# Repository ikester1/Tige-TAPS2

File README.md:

# Replacement Tige TAPS Trim Controller

This is a replacement for the original trim controller for an early 2000's [Tige](https://www.tige.com/) 22v wakeboard boat.
The *electric actuator* is made by [Lenco](https://www.lencomarine.com), the Tige logo'd
trim indicator gauge is probably made by [Faria](https://fariabeede.com), and the
"black box" controller is under the dashboard.  The "black box" takes the trim switch input and drives the actuator
and gauge.  Coupled with a plate on the transom, Tige called the entire system **TAPS2**.

The original controller is prone to failure, and is no longer available from Lenco or Tige.  There are
other solutions from Lenco but there are none which retain the use of the original trim switch and Tige
gauge.

Tige's TAPS controller fully retracts the actuator at each start so one must
reposition the trim at every restart.
This project improves on the original implementation by saving the final actuator position for the next
restart.
If everything works right, the trim will not move and the gauge will be correctly positioned when the
boat is restarted.

The controller's external connections are power and ground, trim switch top/middle/bottom,
gauge power/ground/signal, and two actuator motor power leads.  The controller box has a lighted
setup pushbutton and redundant trim switch.
The box, while deeper than the original controller, has the same footprint.

This project includes the controller's schematic diagram and PCB layout, a 3D printable enclosure, and the C++
controller software.  With access to a 3D printer, the cost of the controller should be less than $75.

# Making the Controller

The replacement controller is a custom processor board connected to a commercial
[H-Bridge](https://en.wikipedia.org/wiki/H-bridge)
to switch the relatively high current actuator connections.
The processor board holds a [Raspberry Pi Pico](https://www.google.com/search?q=raspberry+pico) and surrounding
glue circuitry.

## Processor Board

The [pcb](pcb) directory holds the [KiCad 6](https://www.kicad.org/) files detailing the schematic and
printed circuit layout, and
[bin/TAPS.zip](bin)
is a
[Gerber](https://en.wikipedia.org/wiki/Gerber_format)
file to send to a printed circuit board
fabricator such as [OSHPARK](https://oshpark.com/).

Almost all components are available at [Digi-Key](https://www.digikey.com/) and the schematic is annotated with
manufacturer and product numbers for each component.
The Pico power supply is from [adafruit](https://www.adafruit.com/product/4683).
In addition to the usual soldering supplies, a special crimper
( [Amazon](https://www.amazon.com/dp/B088NQV8Z3) )
is needed for the board's connectors though
one could skip the connectors and solder the wires to the boards.

## H-Bridge

The commercial H-Bridge is a BTS7960 43A High Power Motor Driver Module and can be purchased on Amazon for less than $10 from
[several souces](https://www.amazon.com/s/?url=search-alias%3Daps&field-keywords=BTS7960+43A+Motor+Driver+Module).
The H-Bridge board has an 8 pin header for its logic connections to the processor board; replace this header with the same locking connector
as the processor board to improve robustness.

## Code

The C++ code is compiled on Linux with the [Raspberry Pi Pico C/C++ SDK](https://datasheets.raspberrypi.com/pico/raspberry-pi-pico-c-sdk.pdf).
Go to the [src](src) directory, type `cmake -B build` followed by `cd build && make` to generate the executable to
copy to the Pico processor as described in the SDK. The most recent executable is [bin/taps.elf](bin).

## Enclosure and Switches

The [box](box) directory holds the [SketchUp](https://www.sketchup.com/) enclosure design files.
[Cura](https://ultimaker.com/software/ultimaker-cura) successfully slices
[bin/boxBottom.stl](bin) and [bin/boxTop.stl](bin)
for an [Ultimaker 3D printer](https://ultimaker.com/) though other slicers and printers should work.
The ABS enclosure's bottom secures the boards and external wires with 2-56 screws, while the top holds the setup button and
auxiliary trim switch.
The auxiliary trim switch is a duplicate of the button used on the throttle of the Tige boat.
It is manufactured by
[E-Switch](https://www.e-switch.com/),
part number
R1966IBLKREDEF,
and available on
[Digi-Key](https://www.digikey.com/short/t0br9zjr)
as part number [EG5445-ND](https://www.digikey.com/short/t0br9zjr).
The 16mm illumated setup pushbutton is available from [adafruit](https://www.adafruit.com/product/1477)
and [amazon](https://www.amazon.com/dp/B0148183D2).

The box top and bottom are held together with two 6.3mm automotive plastic trim fasteners.

## Connections

Connect the three *gauge* wires to the existing Tige TAPS gauge -- these should be the only wires connected to
the gauge terminal posts.  This new black box supplies power to the gauge; **do not** also connect the gauge's power terminal to
the boat's electrical system.  Looking from the rear, the black box gauge *PWR* leads goes on the right, *GND* goes in the middle,
and *SIG* goes on the left.  **Connecting any power lead to the gauge's *SIG* terminal will damage the gauge.**
The spade terminal near the blue cap is for gauge illumination and this connection should go to the lighting circuit
shared with the other instruments.

Connect the black box's two actuator leads to the two leads coming from the Lenco electric actuator.  Polarity
is only important when it comes time to ensure the actuator retracts when the black box thinks it should be
retracting, and extends when the black box thinks it is extending the actuator.  If you get the leads backwards,
they can simply be plugged in the other way.

Connect the three trim switch wires to the boat's trim switch ... on my boat this switch is on the throttle handle.
There is no appreciable current flowing through the trim switch so any secure means of connection (any kind of connector)
should be fine.  Do not otherwise connect the boat's power or ground to these connections.

Finally, connect the black box's power and ground to the electrical system.  The heavy power lead should be connected, most likely,
to the same 15A breaker that was powering the original black box (actually, a 10A breaker is probably adequate).
The other, lighter, power lead should be connected to a switched power source.

# Setup

The black box has a *setup mode* entered by pressing its pushbutton.  The button's LED pulses
when the box is in *setup mode* and goes dark when *setup mode* is exited.  *Setup mode* is automatically exited after one
minute of inactivity, or if the pushbutton is pressed and held for at least two seconds.

As soon as *setup mode* is entered, the actuator should fully retract.
If the actuator extends instead of retracts, simply reverse the actuator leads and try again.
When not in
*setup mode*, pressing the side
of the rocker switch nearest the pushbutton should extend the actuator, the other side of
the rocker switch should retract it.
Similarly, pressing the top of the rocker switch on the throttle should extend the actuator and the bottom half of the
switch should retract it.  Something is wrong with the
throttle's switch or wiring if the box's rocker switch works but the throttle's does not.

The primary purpose of *setup mode* is to calibrate the TAPS gauge.
This is done by manually setting the gauge's fully retracted (wakeboard) and 25% - 50% - 75% - 100% 
extended (slalom) gauge needle positions.
More specifically, the gauge's 8, 6, 4, 2, and 0 readings are adjusted.
Enter *setup mode* to adjust these positions and use the trim switch to set the needle's **8** position.
Press the setup button and set the needle's **6** position.
Press the button and set the **4** position; continue for the **2** and **0** positions.
One should be careful when setting the **0** position: release the trim switch as soon as the
**0** position is reached (do not linger) as doing otherwise will bias the box's idea of when **0** was reached.
*Setup mode* automatically exits once the setup button is pressed after adjusting for the **0** position.

# Operation

The trim switch and TAPS system should operate exactly as the original system, except:
- The new black box remembers the actuator and gauge positions when the boat is shut down.
The original box retracts the actuator and resets the gauge at every boat restart.

- The original black box runs the actuator as long as the trim switch is pressed; this replacement box stops the actuator
once it is 50% beyond the retract or extend limits.
In any case, running the Lenco actuator beyond its limits causes no harm to the actuator.

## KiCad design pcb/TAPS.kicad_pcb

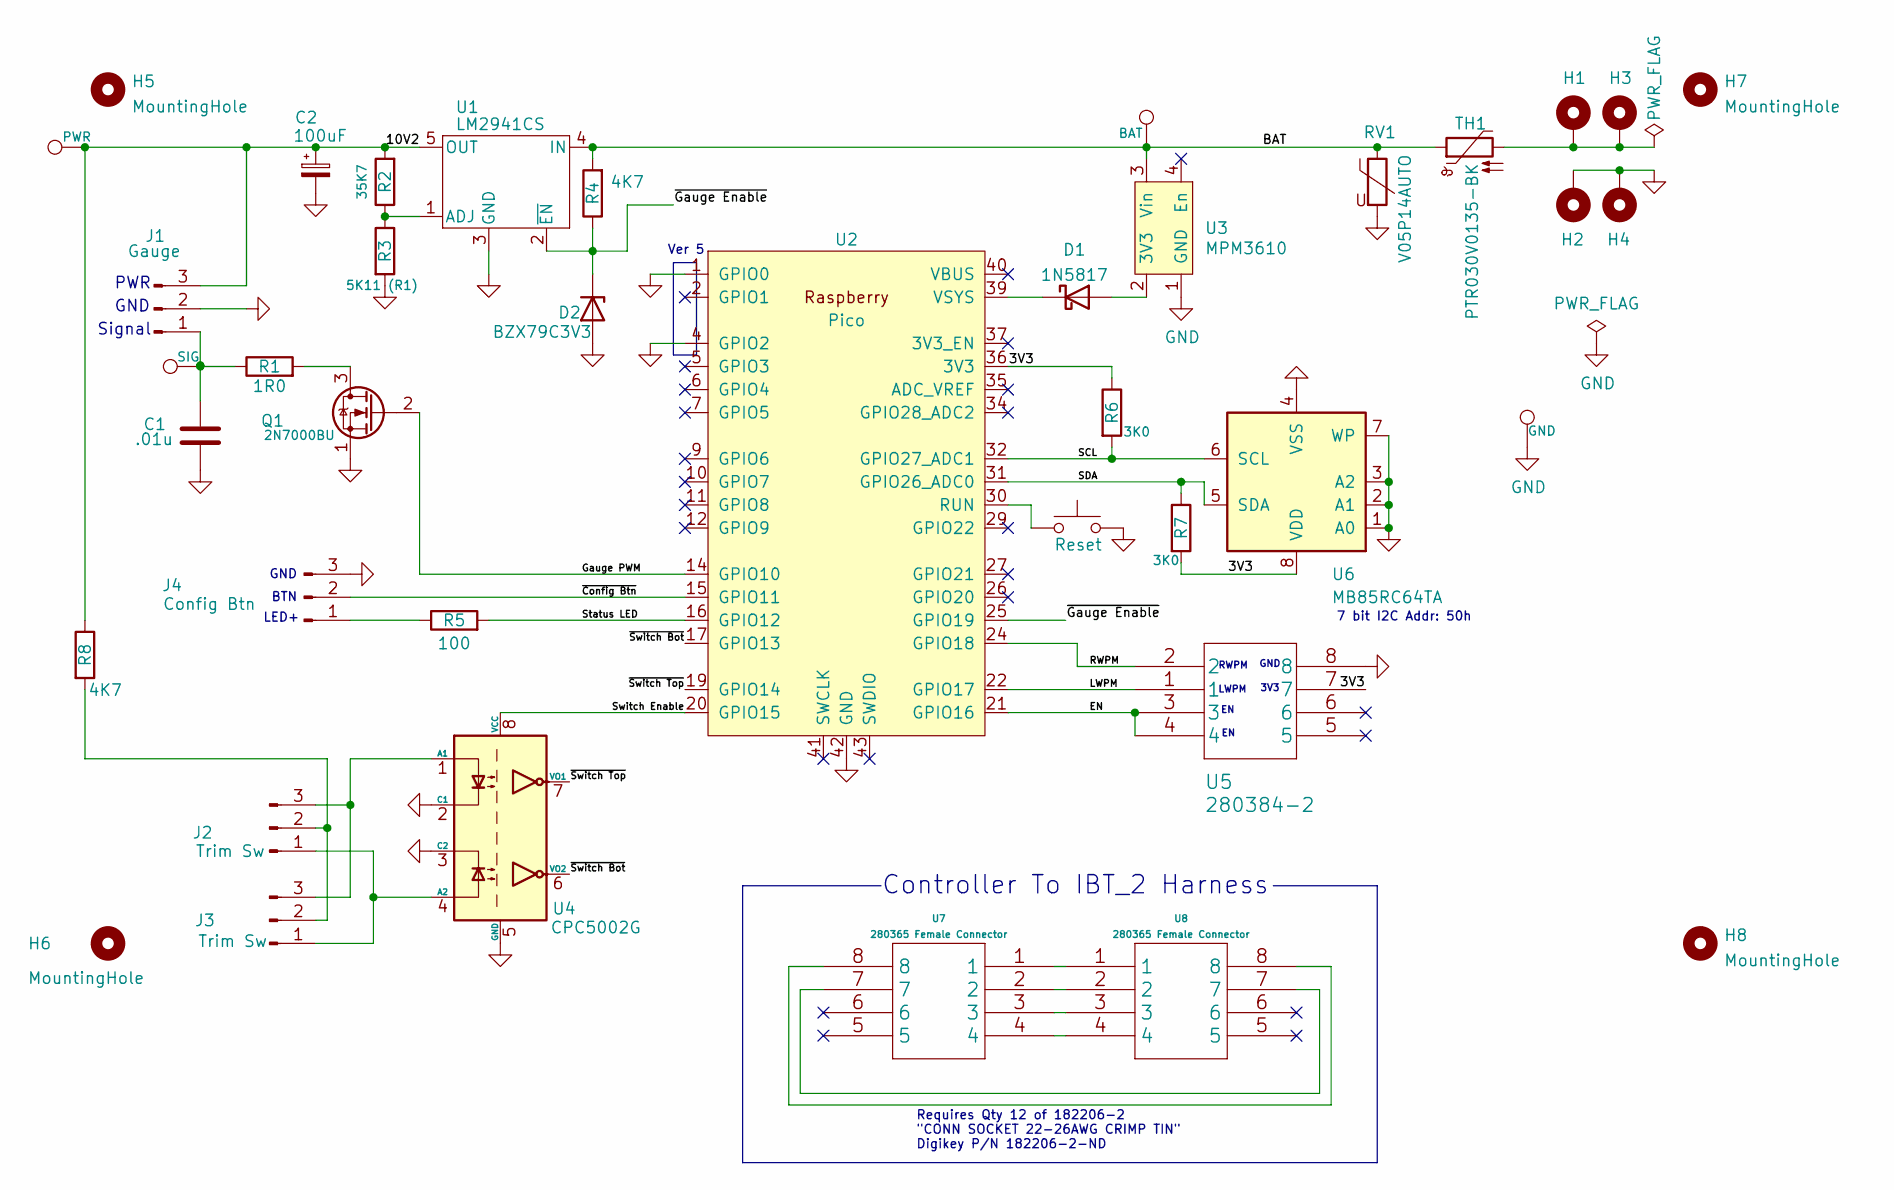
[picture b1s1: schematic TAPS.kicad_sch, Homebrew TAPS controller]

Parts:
C1: .01u; C_Disc_D4.3mm_W1.9mm_P5.00mm; Digikey PN 399-4206-ND
C2: 100uF; C_Disc_D9.0mm_W5.0mm_P5.00mm; Digikey PN 478-1847-ND
D1: 1N5817; D_A-405_P7.62mm_Horizontal; Digikey PN 1N5817RLGOSCT-ND
D2: BZX79C3V3; D_DO-34_SOD68_P7.62mm_Horizontal; Digikey PN BZX79C3V3-ND
H1, H2, H3, H4: MountingHole_Pad; MountingHole_2.5mm_Pad_TopBottom
H5, H6, H7, H8: MountingHole; MountingHole_2.5mm
J1: Gauge; JST_XH_B3B-XH-A_1x03_P2.50mm_Vertical; Digikey PN 455-1990-ND
J2, J3: Trim Sw; JST_XH_B3B-XH-A_1x03_P2.50mm_Vertical; Digikey PN 455-1990-ND
J4: Config Btn; JST_XH_B3B-XH-A_1x03_P2.50mm_Vertical
Q1: 2N7000BU; TO-92_Inline; Digikey PN 2N7000BU-ND
R1: 1R0; R_Axial_DIN0204_L3.6mm_D1.6mm_P7.62mm_Horizontal; Digikey PN CF18JT1R00CT-ND
R2: 35K7; R_Axial_DIN0204_L3.6mm_D1.6mm_P7.62mm_Horizontal; Digikey PN RNF18FTD35K7CT-ND
R3: 5K11 (R1); R_Axial_DIN0204_L3.6mm_D1.6mm_P7.62mm_Horizontal; Digikey PN 738-RNF18FTD5K11CT-ND
R4, R8: 4K7; R_Axial_DIN0204_L3.6mm_D1.6mm_P7.62mm_Horizontal; Digikey PN CF18JT4K70CT-ND
R5: 100; R_Axial_DIN0204_L3.6mm_D1.6mm_P7.62mm_Horizontal; Digikey PN CF18JT100RCT-ND
R6, R7: 3K0; R_Axial_DIN0204_L3.6mm_D1.6mm_P7.62mm_Horizontal; Digikey PN CF18JT3K00CT-ND
RV1: V05P14AUTO; C_Disc_D7.5mm_W5.0mm_P5.00mm; Digikey PN F6411-ND
SW1: Reset; SW_PUSH_6mm_H7.3mm; Digikey PN 450-1650-ND
TH1: PTR030V0135-BK; C_Disc_D10.0mm_W2.5mm_P5.00mm; Digikey PN PTR030V0135-BK-ND
TP1: PWR; TestPoint_Keystone_5000-5004_Miniature; Digikey PN 36-5002-ND
TP2: BAT; TestPoint_Keystone_5000-5004_Miniature; Digikey PN 36-5002-ND
TP3: GND; TestPoint_Keystone_5000-5004_Miniature; Digikey PN 36-5002-ND
TP4: SIG; TestPoint_Keystone_5000-5004_Miniature; Digikey PN 36-5002-ND
U1: LM2941CS; TO-263-5_TabPin3; Digikey PN LM2941CS-ND
U2: Pico; RPi_Pico_SMD; Digikey PN 2648-SC0915CT-ND
U3: MPM3610; Converter_DCDC_Adafruit_MPM3610
U4: CPC5002G; DIP-8_W7.62mm; Digikey PN CLA383-ND
U5: 280384-2; Connector_TE_280384-2; Digikey PN A106409-ND
U6: MB85RC64TA; SOP-8_3.9x4.9mm_P1.27mm; Digikey PN 865-1274-1-ND
U7, U8: 280365 Female Connector; Digikey PN A121748-ND

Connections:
/3V3: R6.1, R7.2, U2.36 (3V3), U5.7, U6.8 (VDD)
/10V2: C2.1, J1.3, R2.2, R8.1, TP1.1, U1.5 (OUT)
/BAT: R4.2, RV1.1, TH1.1, TP2.1, U1.4 (IN), U3.3 (Vin)
/EN: U2.21 (GPIO16), U5.3, U5.4
/Gauge PWM: Q1.2 (G), U2.14 (GPIO10)
/LWPM: U2.22 (GPIO17), U5.1
/RWPM: U2.24 (GPIO18), U5.2
/SCL: R6.2, U2.32 (GPIO27_ADC1), U6.6 (SCL)
/SDA: R7.1, U2.31 (GPIO26_ADC0), U6.5 (SDA)
/Status LED: R5.2, U2.16 (GPIO12)
/Switch Enable: U2.20 (GPIO15), U4.8 (VCC)
/~Config Btn: J4.2, U2.15 (GPIO11)
/~Gauge Enable: D2.1 (K), R4.1, U1.2 (~EN), U2.25 (GPIO19)
/~Switch Bot: U2.17 (GPIO13), U4.6 (VO2)
/~Switch Top: U2.19 (GPIO14), U4.7 (VO1)
GND: C1.2, C2.2, D2.2 (A), H2.1, H4.1, J1.2, J4.3, Q1.1 (S), R3.2, RV1.2, SW1.2, TP3.1, U1.3 (GND), U2.1 (GPIO0), U2.3 (GND), U2.4 (GPIO2), U2.8 (GND), U2.13 (GND), U2.18 (GND), U2.23 (GND), U2.28 (GND), U2.33 (GND), U2.38 (GND), U2.42 (GND), U3.1 (GND), U4.2 (C1), U4.3 (C2), U4.5 (GND), U5.8, U6.1 (A0), U6.2 (A1), U6.3 (A2), U6.4 (VSS), U6.7 (WP)
unnamed: C1.1, J1.1, R1.1, TP4.1
unnamed: D1.1 (K), U2.39 (VSYS)
unnamed: D1.2 (A), U3.2 (3V3)
unnamed: H1.1, H3.1, TH1.2
unnamed: J2.1, J3.1, U4.4 (A2)
unnamed: J2.2, J3.2, R8.2
unnamed: J2.3, J3.3, U4.1 (A1)
unnamed: J4.1, R5.1
unnamed: Q1.3 (D), R1.2
unnamed: R2.1, R3.1, U1.1 (ADJ)
unnamed: SW1.1, U2.30 (RUN)
unnamed: U7.1, U8.1
unnamed: U7.2, U8.2
unnamed: U7.3, U8.3
unnamed: U7.4, U8.4
unnamed: U7.7, U8.7
unnamed: U7.8, U8.8

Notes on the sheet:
Signal
3V3
7 bit I2C Addr: 50h
RWPM
BTN
Requires Qty 12 of 182206-2 "CONN SOCKET 22-26AWG CRIMP TIN" Digikey P/N 182206-2-ND
GND
Ver 5
LED+
LWPM
Controller To IBT_2 Harness
PWR

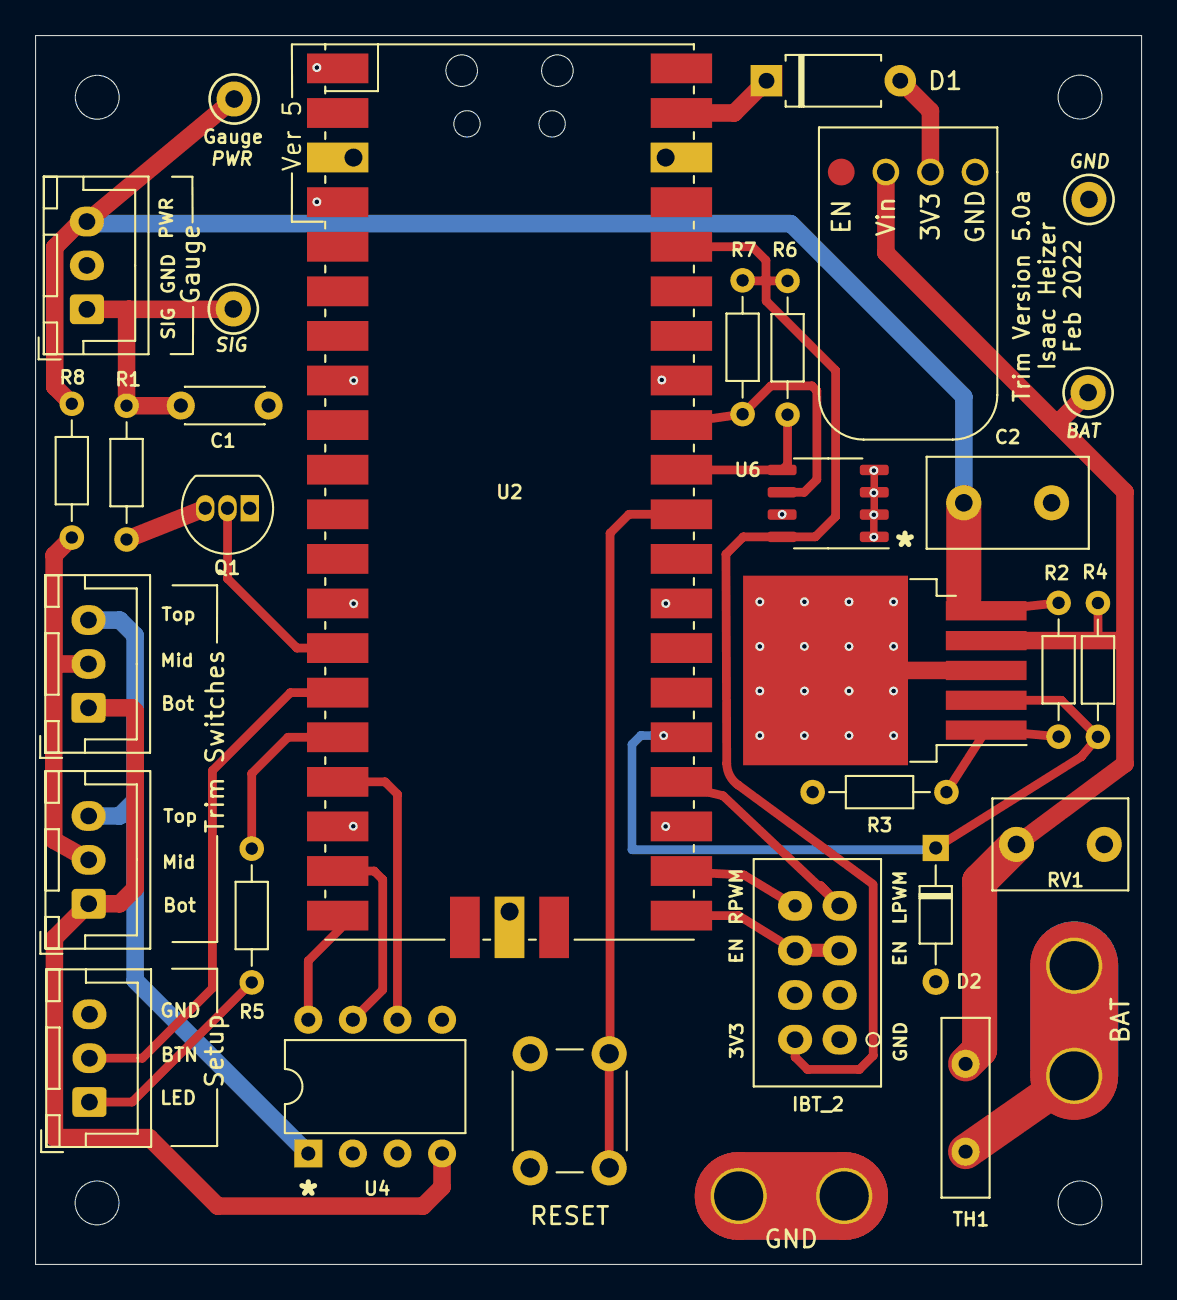
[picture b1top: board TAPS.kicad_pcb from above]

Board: 2 copper layers, 63.0 x 70.0 mm, 38 parts (0 on the bottom side), 27 nets.

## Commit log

2022-02-22 Initial update of README.md, still trying to figure out git
2022-02-24 Updated README.md and renamed the box files
2022-02-24 Add build outputs to the bin directory
2022-03-02 Updated instructions, very minor code changes
2022-03-09 Code and box as installed in my boat
2023-07-20 updated README, added some actuators

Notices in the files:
parts and their libraries:
Copyright 2021 Accelerated Designs. All rights reserved.
